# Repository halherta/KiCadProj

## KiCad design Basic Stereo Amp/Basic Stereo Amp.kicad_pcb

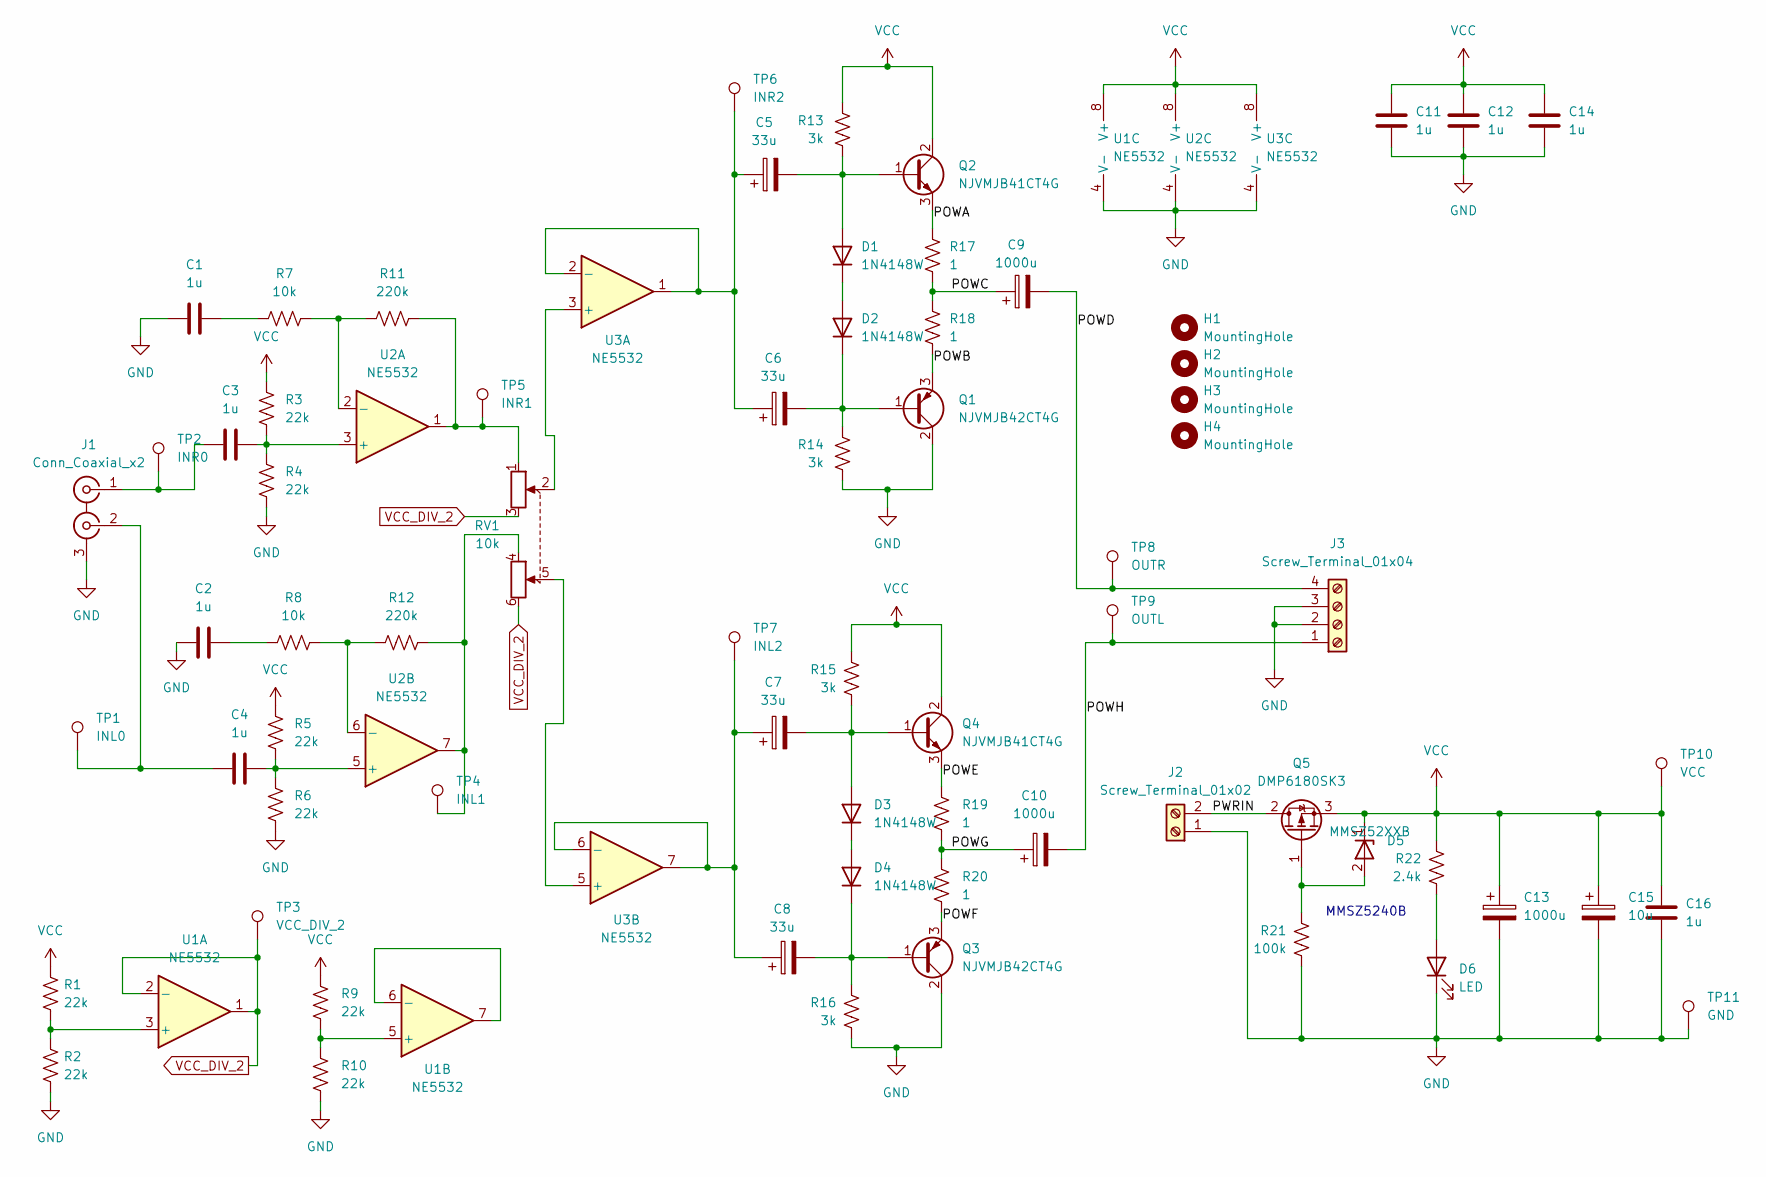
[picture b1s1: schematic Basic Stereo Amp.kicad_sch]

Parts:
C1, C2, C3, C4, C11, C12, C14, C16: 1u; C_1206_3216Metric_Pad1.33x1.80mm_HandSolder
C5, C6, C7, C8: 33u; C_Elec_6.3x5.4
C9, C10, C13: 1000u; CP_Elec_16x17.5
C15: 10u; CP_Elec_5x5.3
D1, D2, D3, D4: 1N4148W; D_SOD-123
D5: MMSZ52XXB; D_SOD-123
D6: LED; LED_1206_3216Metric_Pad1.42x1.75mm_HandSolder
H1, H2, H3, H4: MountingHole; MountingHole_3.2mm_M3_ISO7380
J1: Conn_Coaxial_x2; RCJ-2223
J2: Screw_Terminal_01x02; TerminalBlock_Altech_AK300-2_P5.00mm
J3: Screw_Terminal_01x04; TerminalBlock_Altech_AK300-4_P5.00mm
Q1, Q3: NJVMJB42CT4G; TO-263-2
Q2, Q4: NJVMJB41CT4G; TO-263-2
Q5: DMP6180SK3; TO-252-2
R1, R2, R3, R4, R5, R6, R9, R10: 22k; R_1206_3216Metric_Pad1.30x1.75mm_HandSolder
R7, R8: 10k; R_1206_3216Metric_Pad1.30x1.75mm_HandSolder
R11, R12: 220k; R_1206_3216Metric_Pad1.30x1.75mm_HandSolder
R13, R14, R15, R16: 3k; R_1206_3216Metric_Pad1.30x1.75mm_HandSolder
R17, R18, R19, R20: 1; R_2512_6332Metric_Pad1.40x3.35mm_HandSolder
R21: 100k; R_1206_3216Metric_Pad1.30x1.75mm_HandSolder
R22: 2.4k; R_1206_3216Metric_Pad1.30x1.75mm_HandSolder
RV1: 10k; PTD902-2015K-B103
TP1: INL0; TestPoint_THTPad_D2.0mm_Drill1.0mm
TP2: INR0; TestPoint_THTPad_D2.0mm_Drill1.0mm
TP3: VCC_DIV_2; TestPoint_THTPad_D2.0mm_Drill1.0mm
TP4: INL1; TestPoint_THTPad_D2.0mm_Drill1.0mm
TP5: INR1; TestPoint_THTPad_D2.0mm_Drill1.0mm
TP6: INR2; TestPoint_THTPad_D2.0mm_Drill1.0mm
TP7: INL2; TestPoint_THTPad_D2.0mm_Drill1.0mm
TP8: OUTR; TestPoint_THTPad_D2.0mm_Drill1.0mm
TP9: OUTL; TestPoint_THTPad_D2.0mm_Drill1.0mm
TP10: VCC; TestPoint_THTPad_D2.0mm_Drill1.0mm
TP11: GND; TestPoint_THTPad_D2.0mm_Drill1.0mm
U1, U2, U3: NE5532; SOIC-8_3.9x4.9mm_P1.27mm

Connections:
/POWA: Q2.3 (E), R17.1
/POWB: Q1.3 (E), R18.2
/POWC: C9.1, R17.2, R18.1
/POWD: C9.2, J3.4, TP8.1
/POWE: Q4.3 (E), R19.1
/POWF: Q3.3 (E), R20.2
/POWG: C10.1, R19.2, R20.1
/POWH: C10.2, J3.1, TP9.1
/PWRIN: J2.2, Q5.2 (D)
GND: C1.2, C2.2, C11.2, C12.2, C13.2, C14.2, C15.2, C16.2, D6.1 (K), J1.3 (EXT), J2.1, J3.2, J3.3, Q1.2 (C), Q3.2 (C), R2.1, R4.1, R6.1, R10.1, R14.2, R16.2, R21.2, TP11.1, U1.4 (V-), U2.4 (V-), U3.4 (V-)
unnamed: C1.1, R7.1
unnamed: C2.1, R8.1
unnamed: C5.2, D1.2 (A), Q2.1 (B), R13.2
unnamed: D1.1 (K), D2.2 (A)
unnamed: C6.2, D2.1 (K), Q1.1 (B), R14.1
unnamed: C7.2, D3.2 (A), Q4.1 (B), R15.2
unnamed: D3.1 (K), D4.2 (A)
unnamed: C8.2, D4.1 (K), Q3.1 (B), R16.1
unnamed: D5.2 (A), Q5.1 (G), R21.1
unnamed: D6.2 (A), R22.2
unnamed: C3.2, J1.1 (IN1), TP2.1
unnamed: C4.2, J1.2 (IN2), TP1.1
unnamed: R11.2, RV1.1, TP5.1, U2.1
unnamed: R12.2, RV1.4, TP4.1, U2.7
unnamed: R1.1, R2.2, U1.3 (+)
unnamed: R9.1, R10.2, U1.5 (+)
unnamed: U1.6 (-), U1.7
unnamed: C3.1, R3.1, R4.2, U2.3 (+)
unnamed: R7.2, R11.1, U2.2 (-)
unnamed: C4.1, R5.1, R6.2, U2.5 (+)
unnamed: R8.2, R12.1, U2.6 (-)
unnamed: RV1.2, U3.3 (+)
unnamed: C5.1, C6.1, TP6.1, U3.1, U3.2 (-)
unnamed: RV1.5, U3.5 (+)
unnamed: C7.1, C8.1, TP7.1, U3.6 (-), U3.7
VCC: C11.1, C12.1, C13.1, C14.1, C15.1, C16.1, D5.1 (K), Q2.2 (C), Q4.2 (C), Q5.3 (S), R1.2, R3.2, R5.2, R9.2, R13.1, R15.1, R22.1, TP10.1, U1.8 (V+), U2.8 (V+), U3.8 (V+)
VCC_DIV_2: RV1.3, RV1.6, TP3.1, U1.1, U1.2 (-)

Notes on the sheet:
MMSZ5240B

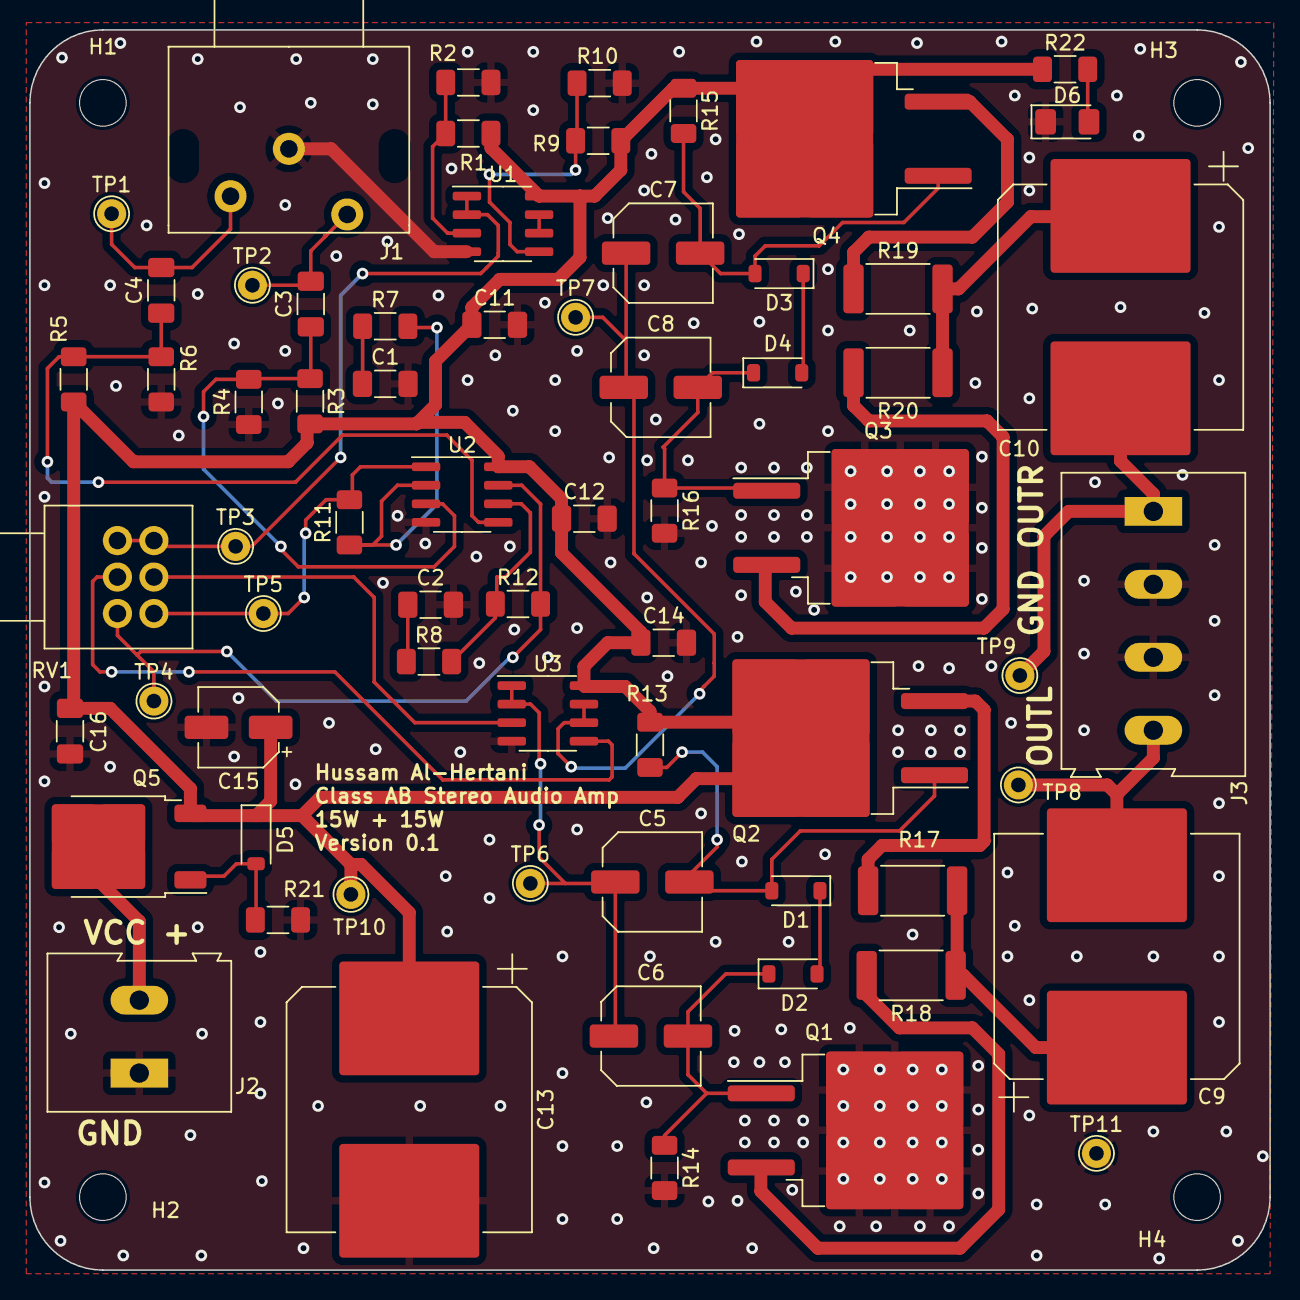
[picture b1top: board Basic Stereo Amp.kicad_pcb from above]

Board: 2 copper layers, 85.0 x 85.0 mm, 71 parts (0 on the bottom side), 37 nets.

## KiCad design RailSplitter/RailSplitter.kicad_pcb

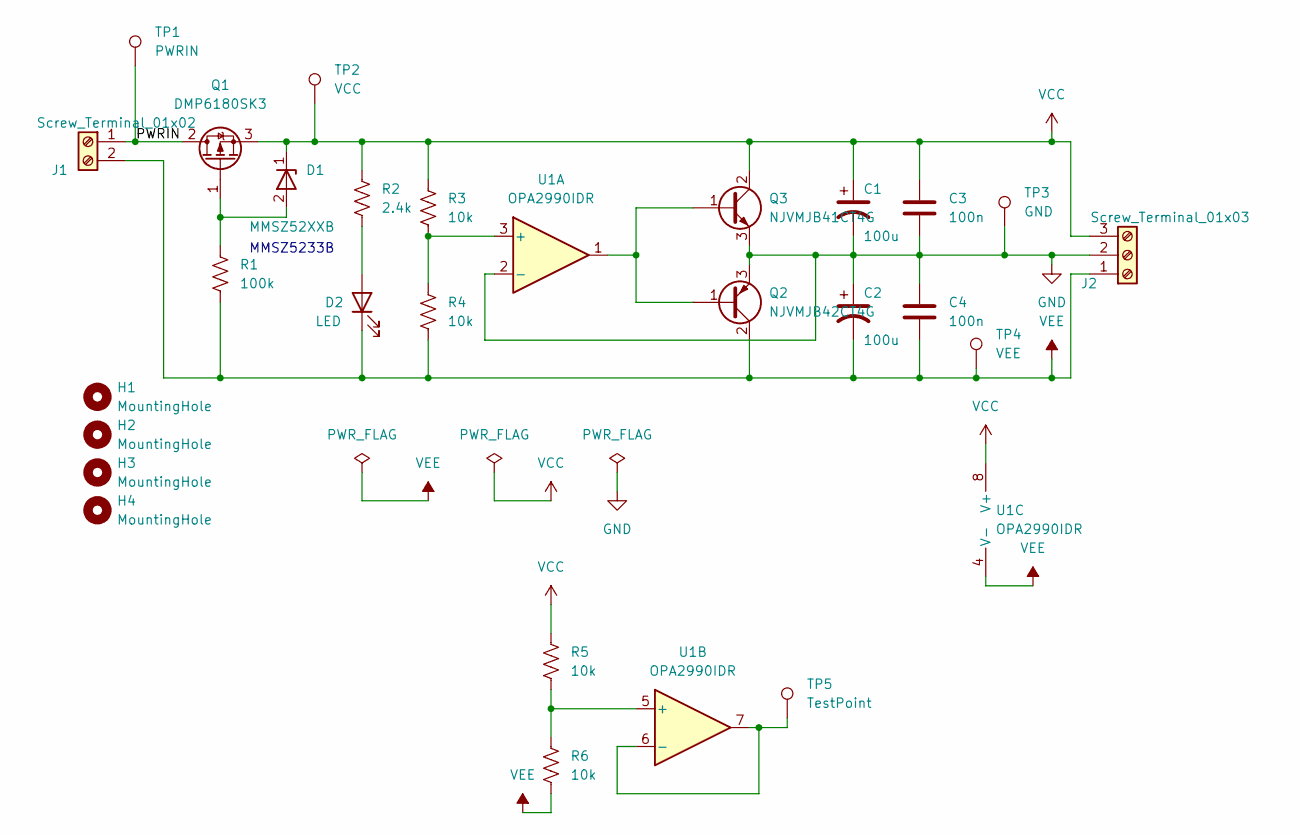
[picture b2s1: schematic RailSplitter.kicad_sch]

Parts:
C1, C2: 100u; CP_Elec_8x10.5
C3, C4: 100n; C_1206_3216Metric_Pad1.33x1.80mm_HandSolder
D1: MMSZ52XXB; D_SOD-123
D2: LED; LED_1206_3216Metric_Pad1.42x1.75mm_HandSolder
H1, H2, H3, H4: MountingHole; MountingHole_3.2mm_M3
J1: Screw_Terminal_01x02; TerminalBlock_Altech_AK300-2_P5.00mm
J2: Screw_Terminal_01x03; TerminalBlock_Altech_AK300-3_P5.00mm
Q1: DMP6180SK3; TO-252-2
Q2: NJVMJB42CT4G; TO-263-2
Q3: NJVMJB41CT4G; TO-263-2
R1: 100k; R_1206_3216Metric_Pad1.30x1.75mm_HandSolder
R2: 2.4k; R_1206_3216Metric_Pad1.30x1.75mm_HandSolder
R3, R4, R5, R6: 10k; R_1206_3216Metric_Pad1.30x1.75mm_HandSolder
TP1: PWRIN; TestPoint_THTPad_D2.0mm_Drill1.0mm
TP2: VCC; TestPoint_THTPad_D2.0mm_Drill1.0mm
TP3: GND; TestPoint_THTPad_D2.0mm_Drill1.0mm
TP4: VEE; TestPoint_THTPad_D2.0mm_Drill1.0mm
TP5: TestPoint; TestPoint_THTPad_D2.0mm_Drill1.0mm
U1: OPA2990IDR; SOIC-8_3.9x4.9mm_P1.27mm

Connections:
/PWRIN: J1.1, Q1.2 (D), TP1.1
GND: C1.2, C2.1, C3.2, C4.1, J2.2, Q2.3 (E), Q3.3 (E), TP3.1, U1.2 (-)
unnamed: D1.2 (A), Q1.1 (G), R1.1
unnamed: D2.2 (A), R2.2
unnamed: Q2.1 (B), Q3.1 (B), U1.1
unnamed: R3.2, R4.1, U1.3 (+)
unnamed: R5.2, R6.1, U1.5 (+)
unnamed: TP5.1, U1.6 (-), U1.7
VCC: C1.1, C3.1, D1.1 (K), J2.3, Q1.3 (S), Q3.2 (C), R2.1, R3.1, R5.1, TP2.1, U1.8 (V+)
VEE: C2.2, C4.2, D2.1 (K), J1.2, J2.1, Q2.2 (C), R1.2, R4.2, R6.2, TP4.1, U1.4 (V-)

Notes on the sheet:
MMSZ5233B

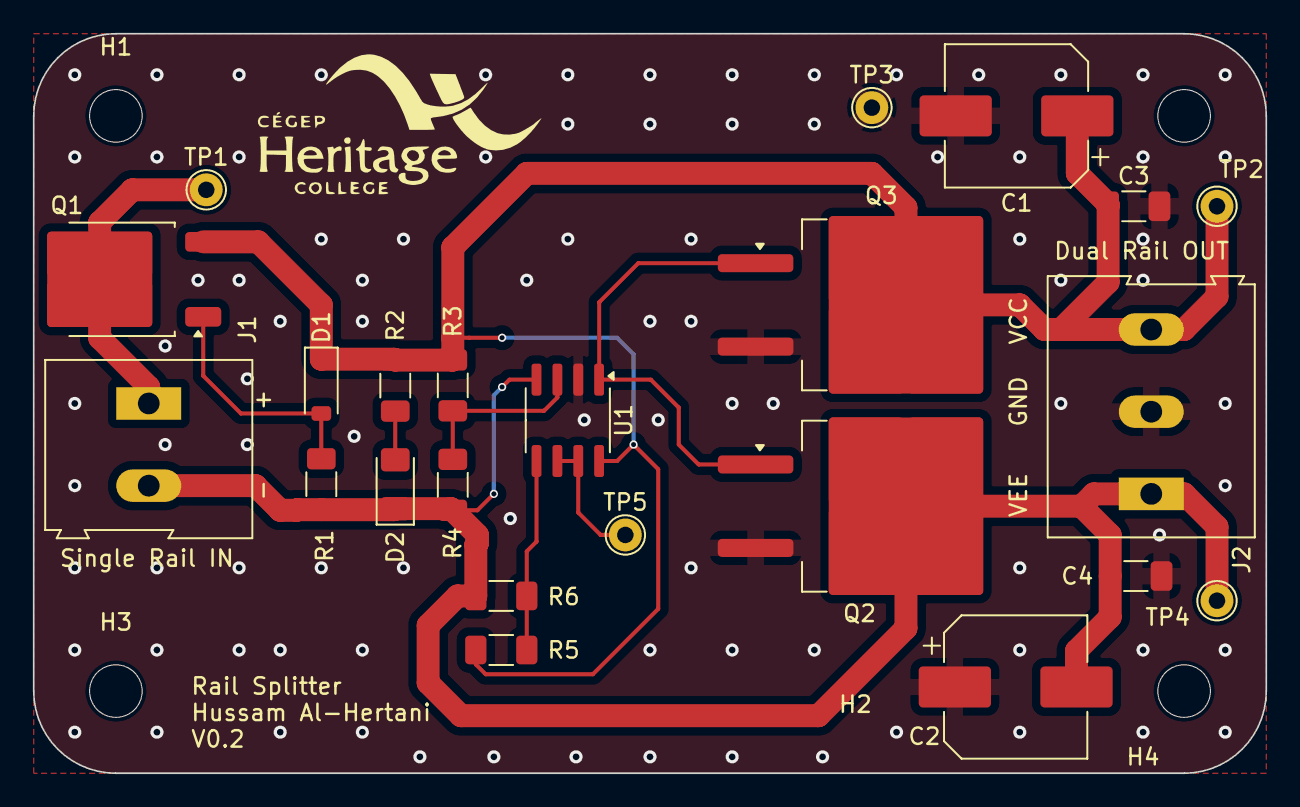
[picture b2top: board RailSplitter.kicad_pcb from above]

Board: 2 copper layers, 75.0 x 45.0 mm, 27 parts (0 on the bottom side), 10 nets.

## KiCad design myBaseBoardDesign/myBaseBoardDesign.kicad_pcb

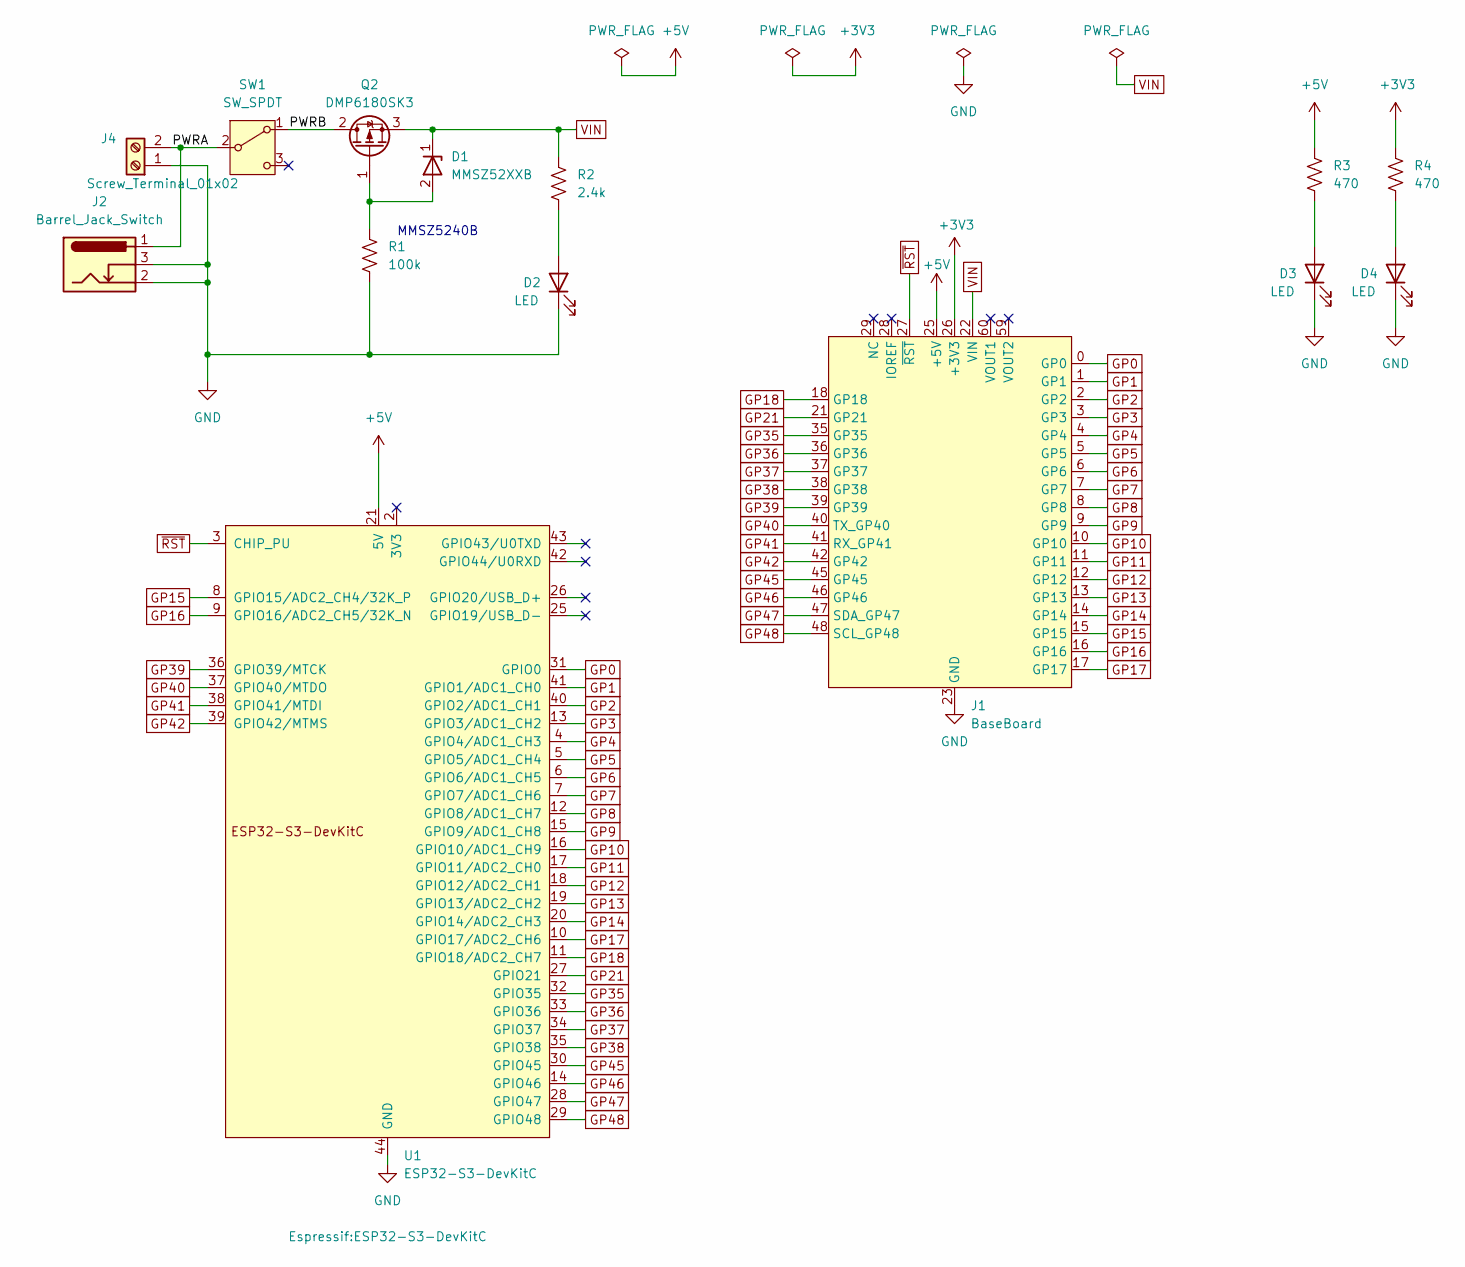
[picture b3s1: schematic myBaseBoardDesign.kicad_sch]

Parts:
D1: MMSZ52XXB; D_SOD-123
D2, D3, D4: LED; LED_1206_3216Metric_Pad1.42x1.75mm_HandSolder
J1: BaseBoard; BaseBoardTemplate
J2: Barrel_Jack_Switch; BarrelJack_CUI_PJ-102AH_Horizontal
J4: Screw_Terminal_01x02; TerminalBlock_Altech_AK300-2_P5.00mm
Q2: DMP6180SK3; TO-252-2
R1: 100k; R_1206_3216Metric_Pad1.30x1.75mm_HandSolder
R2: 2.4k; R_1206_3216Metric_Pad1.30x1.75mm_HandSolder
R3, R4: 470; R_1206_3216Metric_Pad1.30x1.75mm_HandSolder
SW1: SW_SPDT; SW_E-Switch_EG1224_SPDT_Angled
U1: ESP32-S3-DevKitC

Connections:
+3V3: J1.26 (+3V3), J1.32 (+3V3), J1.62 (+3V3), R4.1
+5V: J1.25 (+5V), J1.61 (+5V), R3.1, U1.21 (5V)
/PWRA: J2.1, J4.2, SW1.2 (B)
/PWRB: Q2.2 (D), SW1.1 (A)
GND: D2.1 (K), D3.1 (K), D4.1 (K), J1.23 (GND), J1.24 (GND), J1.30 (GND), J1.55 (GND), J1.56 (GND), J1.57 (GND), J1.58 (GND), J2.2, J2.3, J4.1, R1.2, U1.22 (GND), U1.23 (GND), U1.24 (GND), U1.44 (GND)
GP0: J1.0 (GP0), U1.31 (GPIO0)
GP1: J1.1 (GP1), U1.41 (GPIO1/ADC1_CH0)
GP2: J1.2 (GP2), U1.40 (GPIO2/ADC1_CH1)
GP3: J1.3 (GP3), U1.13 (GPIO3/ADC1_CH2)
GP4: J1.4 (GP4), U1.4 (GPIO4/ADC1_CH3)
GP5: J1.5 (GP5), U1.5 (GPIO5/ADC1_CH4)
GP6: J1.6 (GP6), U1.6 (GPIO6/ADC1_CH5)
GP7: J1.7 (GP7), U1.7 (GPIO7/ADC1_CH6)
GP8: J1.8 (GP8), U1.12 (GPIO8/ADC1_CH7)
GP9: J1.9 (GP9), U1.15 (GPIO9/ADC1_CH8)
GP10: J1.10 (GP10), U1.16 (GPIO10/ADC1_CH9)
GP11: J1.11 (GP11), U1.17 (GPIO11/ADC2_CH0)
GP12: J1.12 (GP12), U1.18 (GPIO12/ADC2_CH1)
GP13: J1.13 (GP13), U1.19 (GPIO13/ADC2_CH2)
GP14: J1.14 (GP14), U1.20 (GPIO14/ADC2_CH3)
GP15: J1.15 (GP15), U1.8 (GPIO15/ADC2_CH4/32K_P)
GP16: J1.16 (GP16), U1.9 (GPIO16/ADC2_CH5/32K_N)
GP17: J1.17 (GP17), U1.10 (GPIO17/ADC2_CH6)
GP18: J1.18 (GP18), U1.11 (GPIO18/ADC2_CH7)
GP21: J1.21 (GP21), U1.27 (GPIO21)
GP35: J1.35 (GP35), U1.32 (GPIO35)
GP36: J1.36 (GP36), U1.33 (GPIO36)
GP37: J1.37 (GP37), U1.34 (GPIO37)
GP38: J1.38 (GP38), U1.35 (GPIO38)
GP39: J1.39 (GP39), U1.36 (GPIO39/MTCK)
GP40: J1.40 (TX_GP40), U1.37 (GPIO40/MTDO)
GP41: J1.41 (RX_GP41), U1.38 (GPIO41/MTDI)
GP42: J1.42 (GP42), U1.39 (GPIO42/MTMS)
GP45: J1.45 (GP45), U1.30 (GPIO45)
GP46: J1.46 (GP46), U1.14 (GPIO46)
GP47: J1.47 (SDA_GP47), U1.28 (GPIO47)
GP48: J1.48 (SCL_GP48), U1.29 (GPIO48)
unnamed: D1.2 (A), Q2.1 (G), R1.1
unnamed: D2.2 (A), R2.2
unnamed: D3.2 (A), R3.2
unnamed: D4.2 (A), R4.2
VIN: D1.1 (K), J1.22 (VIN), J1.53 (VIN), J1.54 (VIN), Q2.3 (S), R2.1
~RST: J1.27 (~RST), U1.3 (CHIP_PU)

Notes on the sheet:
MMSZ5240B

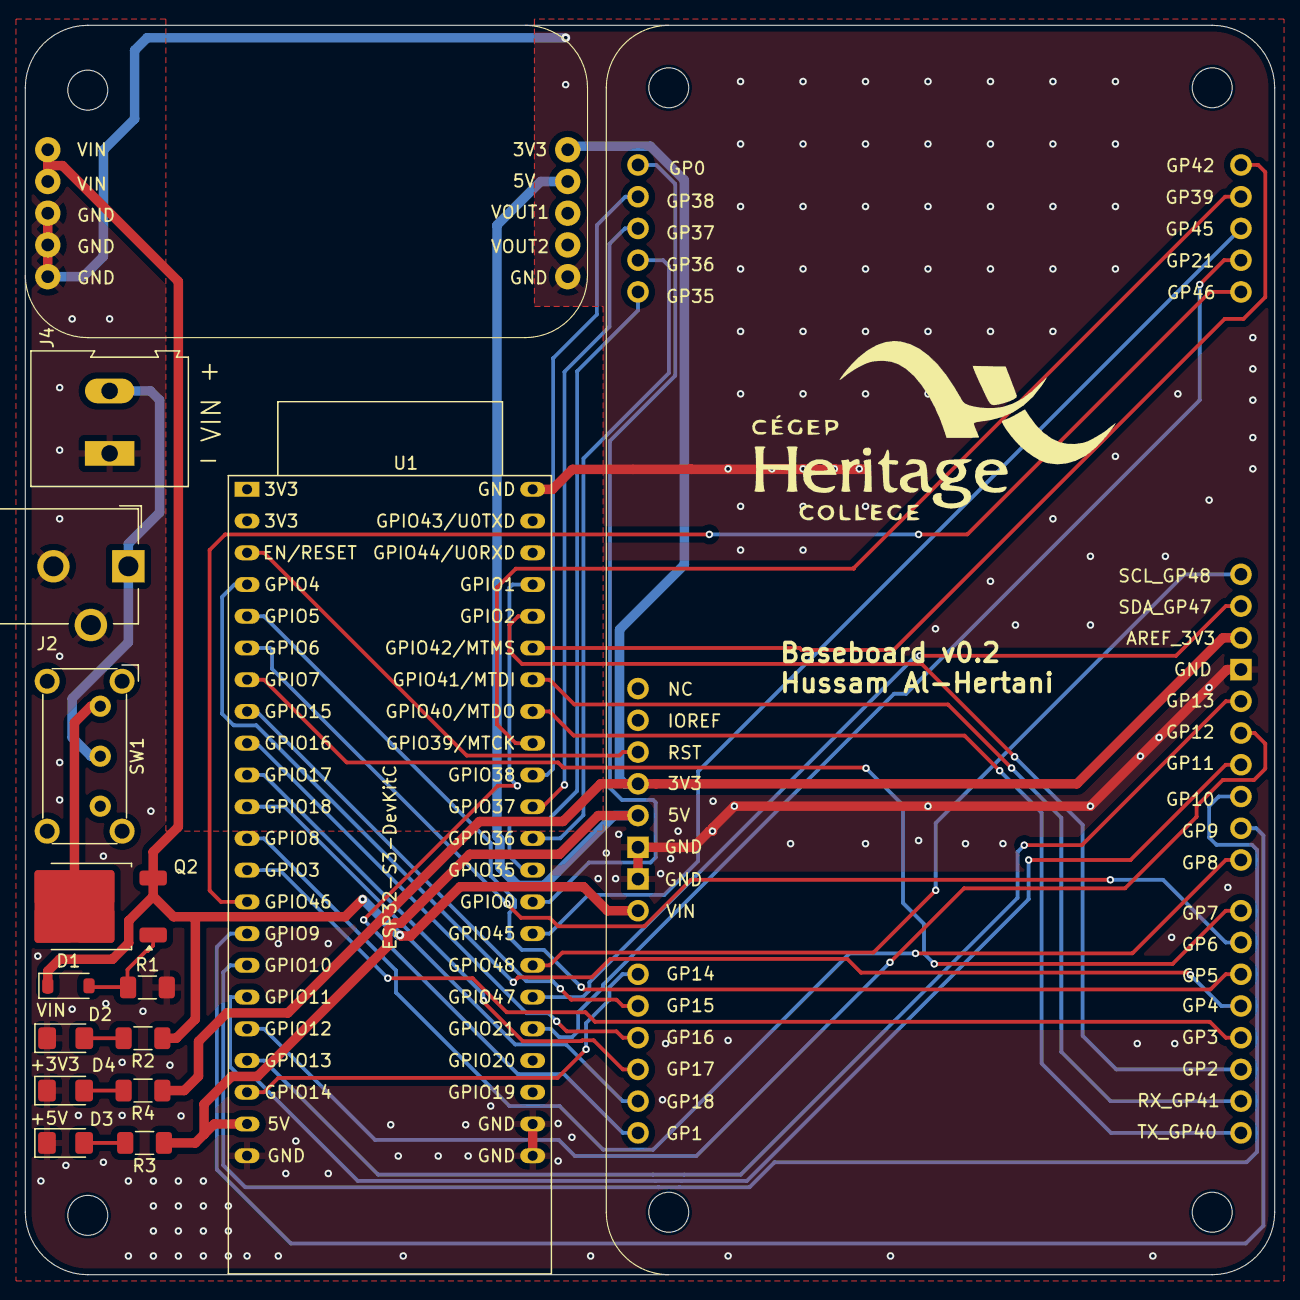
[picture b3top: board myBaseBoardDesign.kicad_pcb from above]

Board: 2 copper layers, 100.0 x 100.0 mm, 14 parts (0 on the bottom side), 43 nets.

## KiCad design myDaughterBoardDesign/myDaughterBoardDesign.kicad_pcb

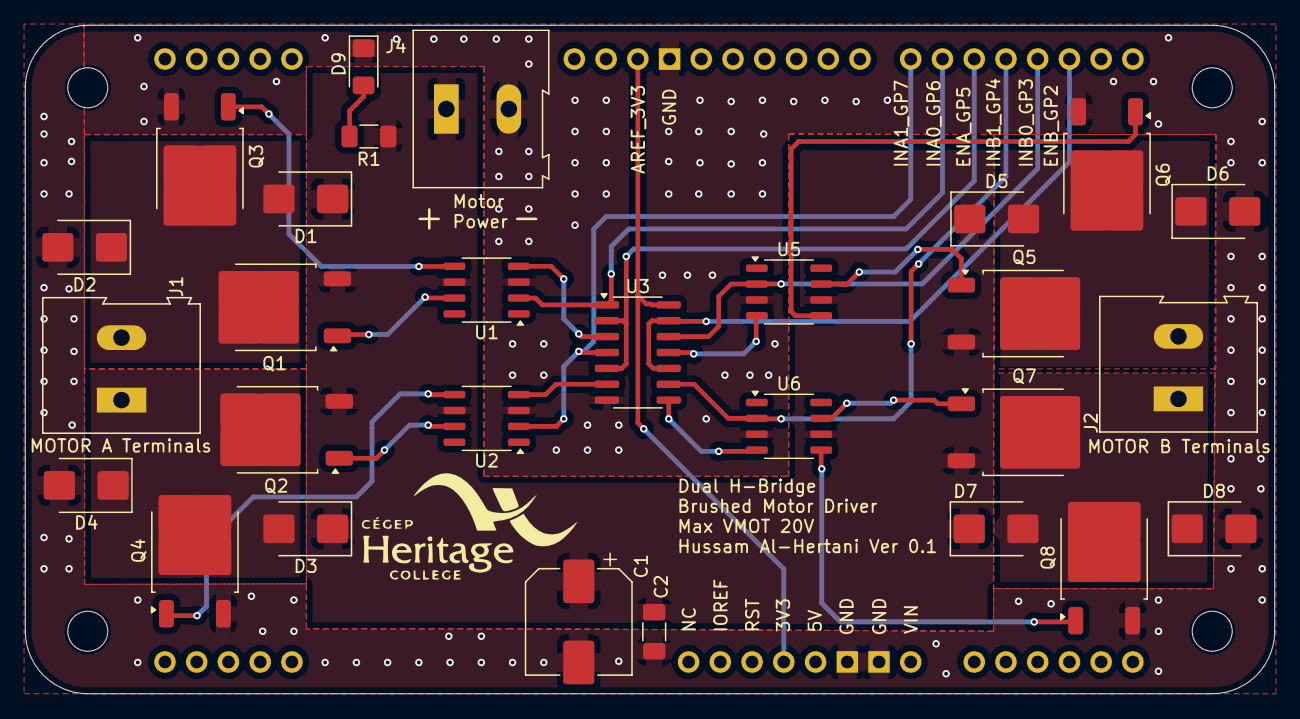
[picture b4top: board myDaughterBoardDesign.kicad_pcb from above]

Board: 2 copper layers, 100.0 x 53.5 mm, 29 parts (0 on the bottom side), 26 nets.

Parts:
C1: 330u; CP_Elec_8x10
C2: 0.1u; C_1206_3216Metric_Pad1.33x1.80mm_HandSolder
D1, D2, D3, D4, D5, D6, D7, D8: B250; D_SMB
D9: LED; LED_1206_3216Metric_Pad1.42x1.75mm_HandSolder
J1, J2, J4: Screw_Terminal_01x02; TerminalBlock_Altech_AK300-2_P5.00mm
J3: DaughterBoard; DaughterBoardTemplate
Q1, Q2, Q5, Q7: AOD4189; TO-252-2
Q3, Q4, Q6, Q8: AOD66406; TO-252-2
R1: 1.6k; R_1206_3216Metric_Pad1.30x1.75mm_HandSolder
U1, U2, U5, U6: MIC4427; SO-8_3.9x4.9mm_P1.27mm
U3: 74HC08; SO-14_3.9x8.65mm_P1.27mm

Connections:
+3V3: J3.26 (+3V3), J3.32 (+3V3), U3.14 (VCC)
/POWA: D1.2 (A), D2.1 (K), J1.2, Q1.2 (D), Q3.2 (D)
/POWB: D3.2 (A), D4.1 (K), J1.1, Q2.2 (D), Q4.2 (D)
/POWC: D5.2 (A), D6.1 (K), J2.2, Q5.2 (D), Q6.2 (D)
/POWD: D7.2 (A), D8.1 (K), J2.1, Q7.2 (D), Q8.2 (D)
ENA: J3.5 (GP5), U3.2, U3.5
ENB: J3.2 (GP2), U3.10, U3.13
GND: C1.2, C2.2, D2.2 (A), D4.2 (A), D6.2 (A), D8.2 (A), D9.1 (K), J3.23 (GND), J3.24 (GND), J3.30 (GND), J4.2, Q3.3 (S), Q4.3 (S), Q6.3 (S), Q8.3 (S), U1.3 (GND), U2.3 (GND), U3.7 (GND), U5.3 (GND), U6.3 (GND)
INA0: J3.6 (GP6), U1.2 (IN_A), U3.1
INA1: J3.7 (GP7), U2.2 (IN_A), U3.4
INB0: J3.3 (GP3), U3.12, U5.2 (IN_A)
INB1: J3.4 (GP4), U3.9, U6.2 (IN_A)
unnamed: D9.2 (A), R1.2
unnamed: Q1.1 (G), U1.7 (OUT_A)
unnamed: Q2.1 (G), U2.7 (OUT_A)
unnamed: Q3.1 (G), U1.5 (OUT_B)
unnamed: Q4.1 (G), U2.5 (OUT_B)
unnamed: Q5.1 (G), U5.7 (OUT_A)
unnamed: Q6.1 (G), U5.5 (OUT_B)
unnamed: Q7.1 (G), U6.7 (OUT_A)
unnamed: Q8.1 (G), U6.5 (OUT_B)
unnamed: U1.4 (IN_B), U3.3
unnamed: U2.4 (IN_B), U3.6
unnamed: U3.11, U5.4 (IN_B)
unnamed: U3.8, U6.4 (IN_B)
Vdrive: C1.1, C2.1, D1.1 (K), D3.1 (K), D5.1 (K), D7.1 (K), J4.1, Q1.3 (S), Q2.3 (S), Q5.3 (S), Q7.3 (S), R1.1, U1.6 (V+), U2.6 (V+), U5.6 (V+), U6.6 (V+)
